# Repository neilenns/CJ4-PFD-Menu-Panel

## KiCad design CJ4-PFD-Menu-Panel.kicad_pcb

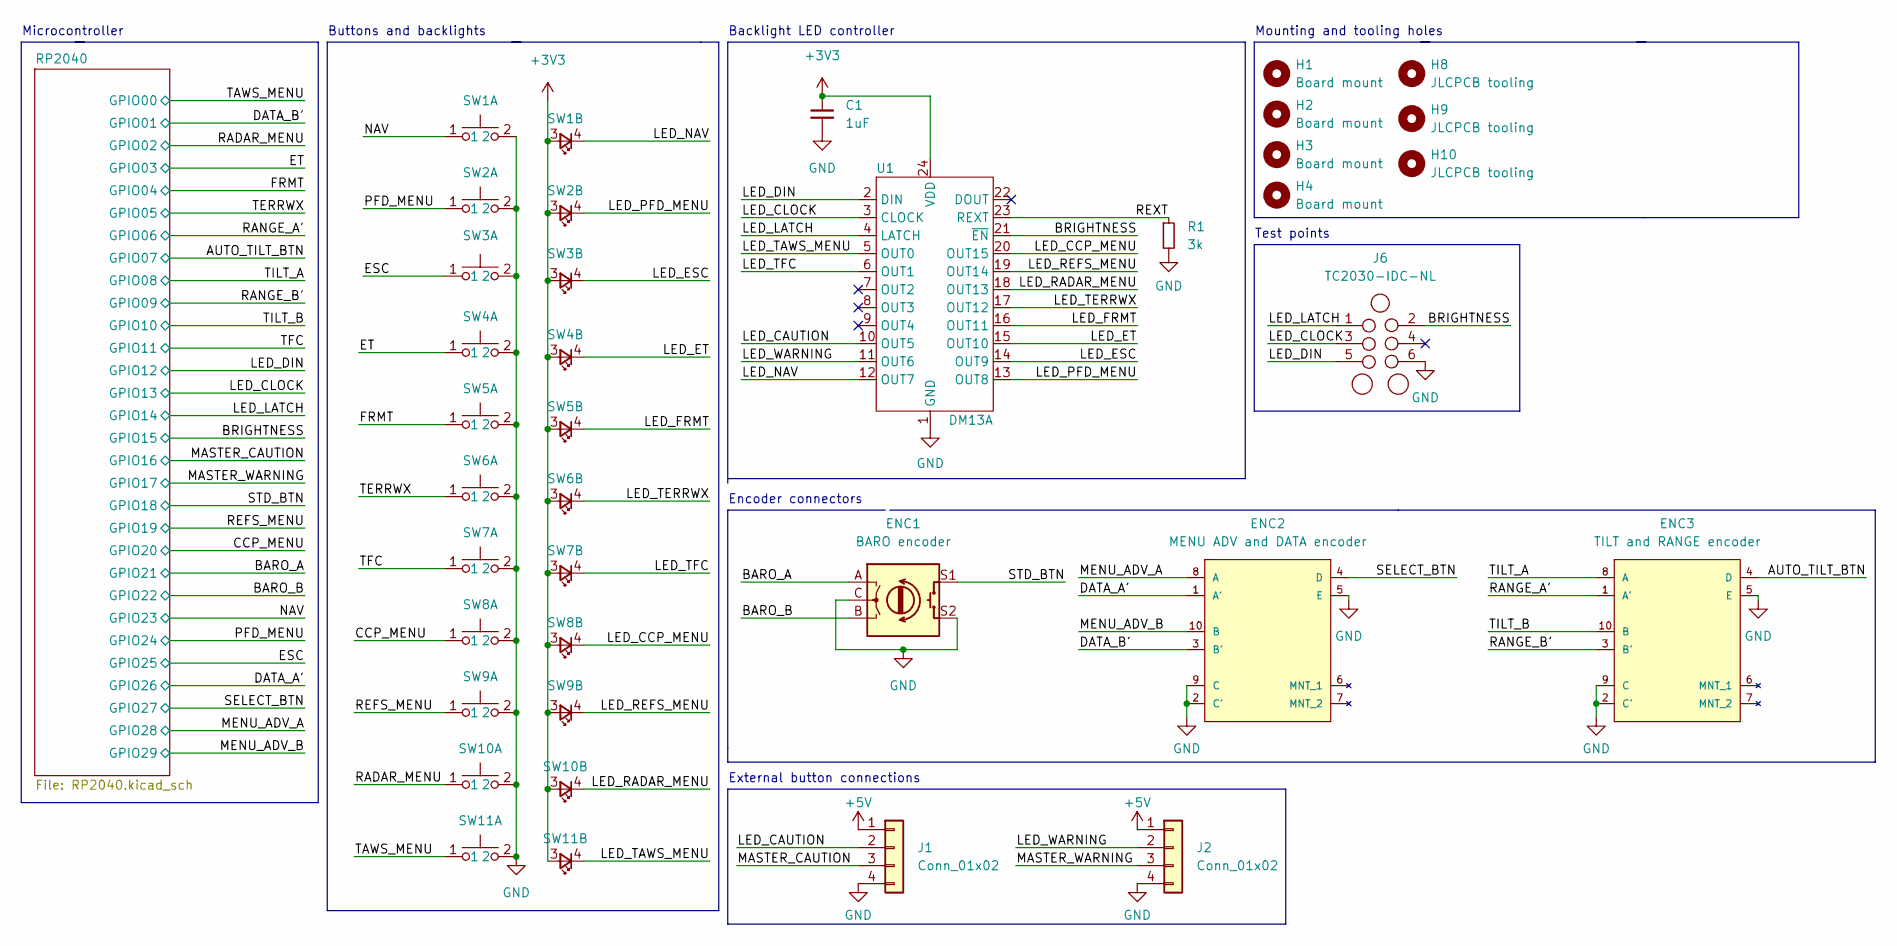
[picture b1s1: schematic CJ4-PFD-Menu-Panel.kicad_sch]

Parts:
C1: 1uF; Perfect_0402; JLC 0402
ENC1: BARO encoder; EN11-HSM1BF20_THT
ENC2: MENU ADV and DATA encoder; ALPS-EC11EBB24C03-0; Rating 10mA 5VDC; mouser part number 688-EC11EBB24C03
ENC3: TILT and RANGE encoder; ALPS-EC11EBB24C03-0; Rating 10mA 5VDC; mouser part number 688-EC11EBB24C03
H1, H2, H3, H4: Board mount; MountingHole_3.2mm_M3
H8, H9, H10: JLCPCB tooling; JLCPCB_Tooling_Hole
J1, J2: Conn_01x02; JST_XH_B4B-XH-A_1x04_P2.50mm_Vertical
J6: TC2030-IDC-NL; Tag-Connect_TC2030-IDC-NL_2x03_P1.27mm_Vertical
R1: 3k; R_0805_2012Metric_Pad1.20x1.40mm_HandSolder; JLC 0805
SW1, SW2, SW3, SW4, SW5, SW6, SW7, SW8, SW9, SW10, SW11: SW_PUSH_LED; SW_PUSH_LED_THT
U1: DM13A; SSOP-24_3.9x8.7mm_P0.635mm

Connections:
+3V3: C1.1, SW1.3, SW2.3, SW3.3, SW4.3, SW5.3, SW6.3, SW7.3, SW8.3, SW9.3, SW10.3, SW11.3, U1.24 (VDD); also elsewhere on the board
+5V: J1.1, J2.1; also elsewhere on the board
/AUTO_TILT_BTN: ENC3.4 (D); also elsewhere on the board
/BARO_A: ENC1.A; also elsewhere on the board
/BARO_B: ENC1.B; also elsewhere on the board
/BRIGHTNESS: J6.2, U1.21 (~EN); also elsewhere on the board
/CCP_MENU: SW8.1; also elsewhere on the board
/DATA_A': ENC2.1 (A'); also elsewhere on the board
/DATA_B': ENC2.3 (B'); also elsewhere on the board
/ESC: SW3.1; also elsewhere on the board
/ET: SW4.1; also elsewhere on the board
/FRMT: SW5.1; also elsewhere on the board
/LED_CAUTION: J1.2, U1.10 (OUT5)
/LED_CCP_MENU: SW8.4, U1.20 (OUT15)
/LED_CLOCK: J6.3, U1.3 (CLOCK); also elsewhere on the board
/LED_DIN: J6.5, U1.2 (DIN); also elsewhere on the board
/LED_ESC: SW3.4, U1.14 (OUT9)
/LED_ET: SW4.4, U1.15 (OUT10)
/LED_FRMT: SW5.4, U1.16 (OUT11)
/LED_LATCH: J6.1, U1.4 (LATCH); also elsewhere on the board
/LED_NAV: SW1.4, U1.12 (OUT7)
/LED_PFD_MENU: SW2.4, U1.13 (OUT8)
/LED_RADAR_MENU: SW10.4, U1.18 (OUT13)
/LED_REFS_MENU: SW9.4, U1.19 (OUT14)
/LED_TAWS_MENU: SW11.4, U1.5 (OUT0)
/LED_TERRWX: SW6.4, U1.17 (OUT12)
/LED_TFC: SW7.4, U1.6 (OUT1)
/LED_WARNING: J2.2, U1.11 (OUT6)
/MASTER_CAUTION: J1.3; also elsewhere on the board
/MASTER_WARNING: J2.3; also elsewhere on the board
/MENU_ADV_A: ENC2.8 (A); also elsewhere on the board
/MENU_ADV_B: ENC2.10 (B); also elsewhere on the board
/NAV: SW1.1; also elsewhere on the board
/PFD_MENU: SW2.1; also elsewhere on the board
/RADAR_MENU: SW10.1; also elsewhere on the board
/RANGE_A': ENC3.1 (A'); also elsewhere on the board
/RANGE_B': ENC3.3 (B'); also elsewhere on the board
/REFS_MENU: SW9.1; also elsewhere on the board
/REXT: R1.1, U1.23 (REXT)
/SELECT_BTN: ENC2.4 (D); also elsewhere on the board
/STD_BTN: ENC1.S1; also elsewhere on the board
/TAWS_MENU: SW11.1; also elsewhere on the board
/TERRWX: SW6.1; also elsewhere on the board
/TFC: SW7.1; also elsewhere on the board
/TILT_A: ENC3.8 (A); also elsewhere on the board
/TILT_B: ENC3.10 (B); also elsewhere on the board
GND: C1.2, ENC1.C, ENC1.S2, ENC2.2 (C'), ENC2.5 (E), ENC2.9 (C), ENC3.2 (C'), ENC3.5 (E), ENC3.9 (C), J1.4, J2.4, J6.6, R1.2, SW1.2, SW2.2, SW3.2, SW4.2, SW5.2, SW6.2, SW7.2, SW8.2, SW9.2, SW10.2, SW11.2, U1.1 (GND); also elsewhere on the board

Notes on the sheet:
Mounting and tooling holes
Microcontroller
Buttons and backlights
Backlight LED controller
Test points
Encoder connectors
External button connections

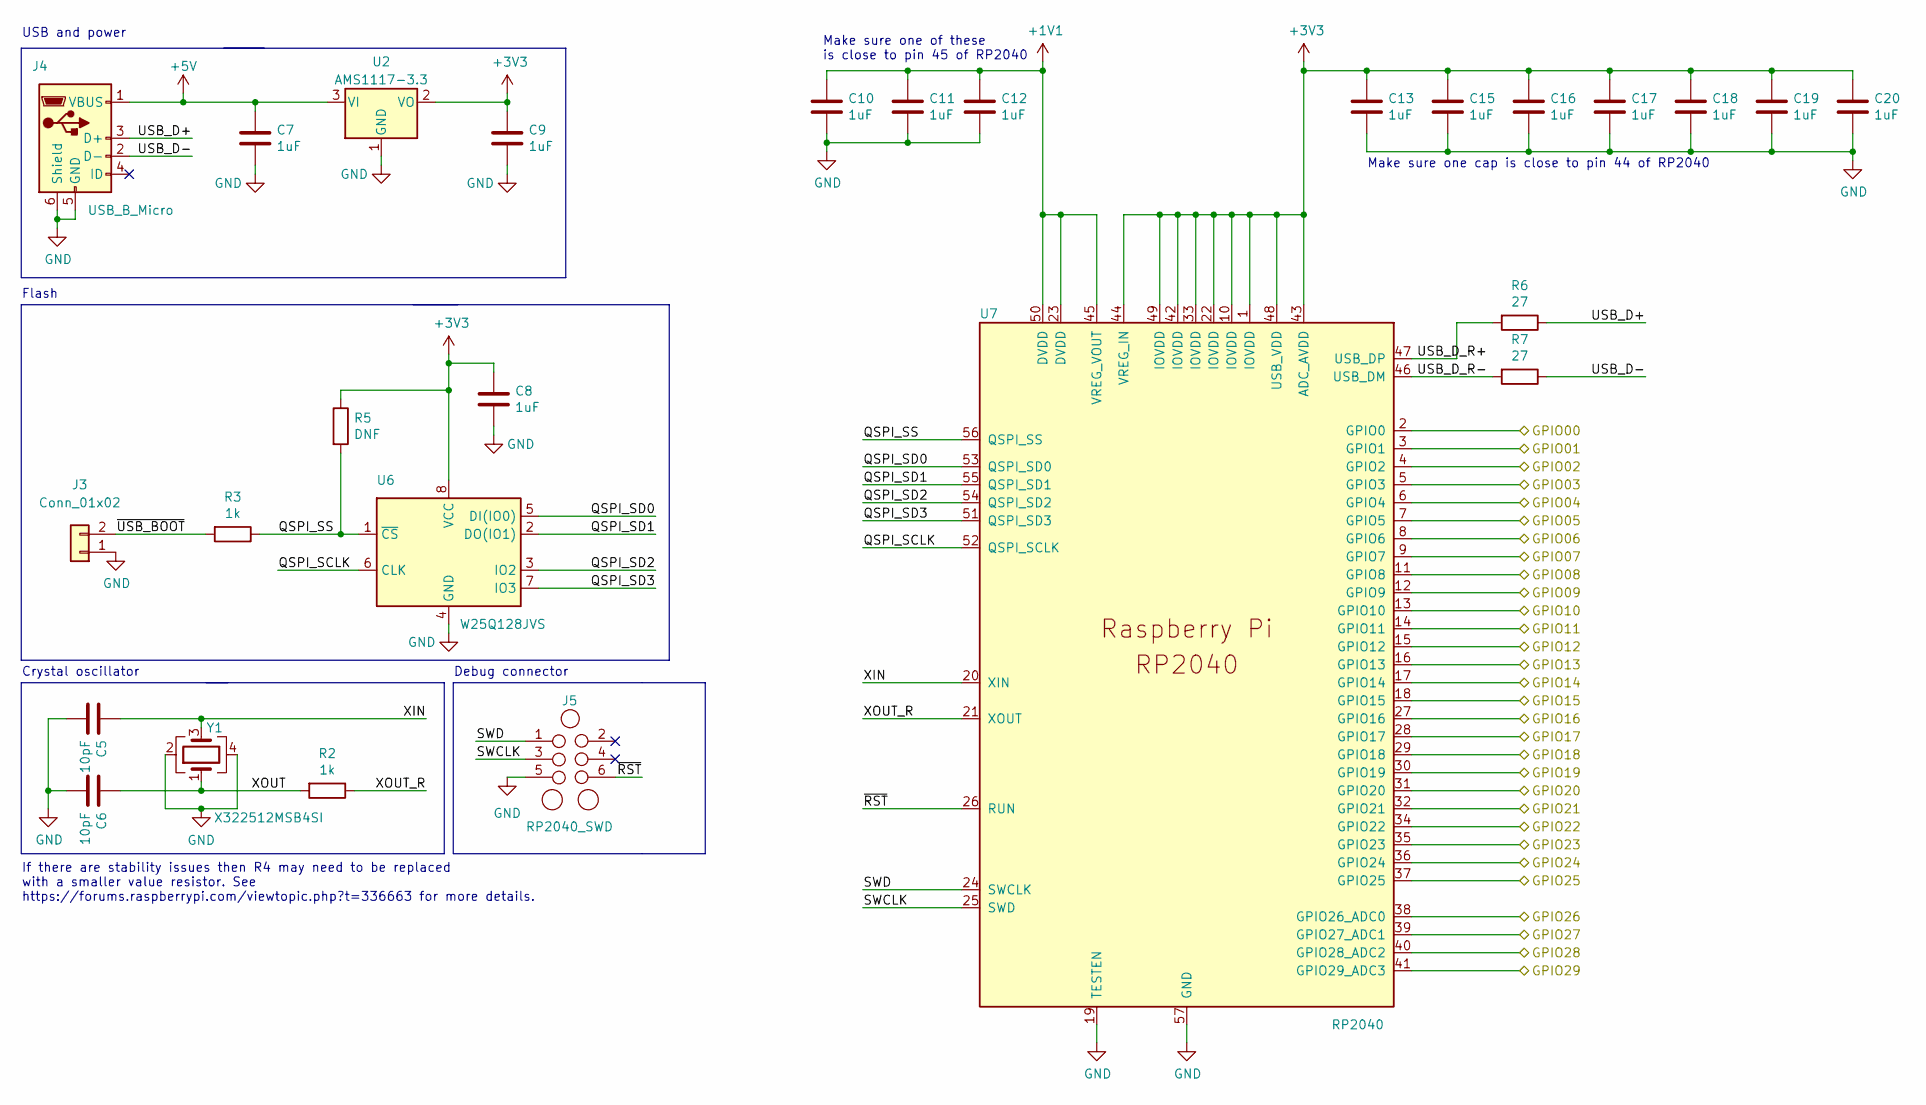
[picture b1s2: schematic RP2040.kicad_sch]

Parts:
C5, C6: 10pF; Perfect_0402; JLC 0402
C7, C8, C9, C10, C11, C12, C13, C15, C16, C17, C18, C19, C20: 1uF; Perfect_0402; JLC 0402
J3: Conn_01x02; PinHeader_1x02_P2.54mm_Vertical
J4: USB_B_Micro; USB_B_Mini_Amphenol_UE25BE5510H
J5: RP2040_SWD; Tag-Connect_TC2030-IDC-NL_2x03_P1.27mm_Vertical
R2, R3: 1k; Perfect_0402; JLC 0402
R5: DNF; R_1206_3216Metric_Pad1.30x1.75mm_HandSolder
R6, R7: 27; R_0603_1608Metric; JLC 0603
U2: AMS1117-3.3; SOT-223-3_TabPin2; JLC SOT-223
U6: W25Q128JVS; SOIC-8_5.23x5.23mm_P1.27mm; JLC SOIC-8-208mil
U7: RP2040; QFN56P40_700X700X90L40X18T310N; JLC LQFN-56_EP_7.0x7.0x0.4P
Y1: X322512MSB4SI; Crystal_SMD_3225-4Pin_3.2x2.5mm; JLC SMD-3225_4P

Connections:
+1V1: C10.1, C11.1, C12.1, U7.23 (DVDD), U7.45 (VREG_VOUT), U7.50 (DVDD)
+3V3: C8.1, C9.1, C13.1, C15.1, C16.1, C17.1, C18.1, C19.1, C20.1, R5.1, U2.2 (VO), U6.8 (VCC), U7.1 (IOVDD), U7.10 (IOVDD), U7.22 (IOVDD), U7.33 (IOVDD), U7.42 (IOVDD), U7.43 (ADC_AVDD), U7.44 (VREG_IN), U7.48 (USB_VDD), U7.49 (IOVDD); also elsewhere on the board
+5V: C7.1, J4.1 (VBUS), U2.3 (VI); also elsewhere on the board
/AUTO_TILT_BTN: U7.9 (GPIO7); also elsewhere on the board
/BARO_A: U7.32 (GPIO21); also elsewhere on the board
/BARO_B: U7.34 (GPIO22); also elsewhere on the board
/BRIGHTNESS: U7.18 (GPIO15); also elsewhere on the board
/CCP_MENU: U7.31 (GPIO20); also elsewhere on the board
/DATA_A': U7.38 (GPIO26_ADC0); also elsewhere on the board
/DATA_B': U7.3 (GPIO1); also elsewhere on the board
/ESC: U7.37 (GPIO25); also elsewhere on the board
/ET: U7.5 (GPIO3); also elsewhere on the board
/FRMT: U7.6 (GPIO4); also elsewhere on the board
/LED_CLOCK: U7.16 (GPIO13); also elsewhere on the board
/LED_DIN: U7.15 (GPIO12); also elsewhere on the board
/LED_LATCH: U7.17 (GPIO14); also elsewhere on the board
/MASTER_CAUTION: U7.27 (GPIO16); also elsewhere on the board
/MASTER_WARNING: U7.28 (GPIO17); also elsewhere on the board
/MENU_ADV_A: U7.40 (GPIO28_ADC2); also elsewhere on the board
/MENU_ADV_B: U7.41 (GPIO29_ADC3); also elsewhere on the board
/NAV: U7.35 (GPIO23); also elsewhere on the board
/PFD_MENU: U7.36 (GPIO24); also elsewhere on the board
/RADAR_MENU: U7.4 (GPIO2); also elsewhere on the board
/RANGE_A': U7.8 (GPIO6); also elsewhere on the board
/RANGE_B': U7.12 (GPIO9); also elsewhere on the board
/REFS_MENU: U7.30 (GPIO19); also elsewhere on the board
/RP2040/QSPI_SCLK: U6.6 (CLK), U7.52 (QSPI_SCLK)
/RP2040/QSPI_SD0: U6.5 (DI(IO0)), U7.53 (QSPI_SD0)
/RP2040/QSPI_SD1: U6.2 (DO(IO1)), U7.55 (QSPI_SD1)
/RP2040/QSPI_SD2: U6.3 (IO2), U7.54 (QSPI_SD2)
/RP2040/QSPI_SD3: U6.7 (IO3), U7.51 (QSPI_SD3)
/RP2040/QSPI_SS: R3.1, R5.2, U6.1 (~CS), U7.56 (QSPI_SS)
/RP2040/SWCLK: J5.3, U7.25 (SWD)
/RP2040/SWD: J5.1, U7.24 (SWCLK)
/RP2040/USB_D+: J4.3 (D+), R6.1
/RP2040/USB_D-: J4.2 (D-), R7.1
/RP2040/USB_D_R+: R6.2, U7.47 (USB_DP)
/RP2040/USB_D_R-: R7.2, U7.46 (USB_DM)
/RP2040/XIN: C5.1, U7.20 (XIN), Y1.3
/RP2040/XOUT: C6.1, R2.2, Y1.1
/RP2040/XOUT_R: R2.1, U7.21 (XOUT)
/RP2040/~RST: J5.6, U7.26 (RUN)
/RP2040/~USB_BOOT: J3.2, R3.2
/SELECT_BTN: U7.39 (GPIO27_ADC1); also elsewhere on the board
/STD_BTN: U7.29 (GPIO18); also elsewhere on the board
/TAWS_MENU: U7.2 (GPIO0); also elsewhere on the board
/TERRWX: U7.7 (GPIO5); also elsewhere on the board
/TFC: U7.14 (GPIO11); also elsewhere on the board
/TILT_A: U7.11 (GPIO8); also elsewhere on the board
/TILT_B: U7.13 (GPIO10); also elsewhere on the board
GND: C5.2, C6.2, C7.2, C8.2, C9.2, C10.2, C11.2, C12.2, C13.2, C15.2, C16.2, C17.2, C18.2, C19.2, C20.2, J3.1, J4.5 (GND), J4.6 (Shield), J5.5, U2.1 (GND), U6.4 (GND), U7.19 (TESTEN), U7.57 (GND), Y1.2, Y1.4; also elsewhere on the board

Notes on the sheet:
If there are stability issues then R4 may need to be replaced with a smaller value resistor. See https://forums.raspberrypi.com/viewtopic.php?t=336663 for more details.
Make sure one cap is close to pin 44 of RP2040
Crystal oscillator
USB and power
Flash
Debug connector
Make sure one of these is close to pin 45 of RP2040

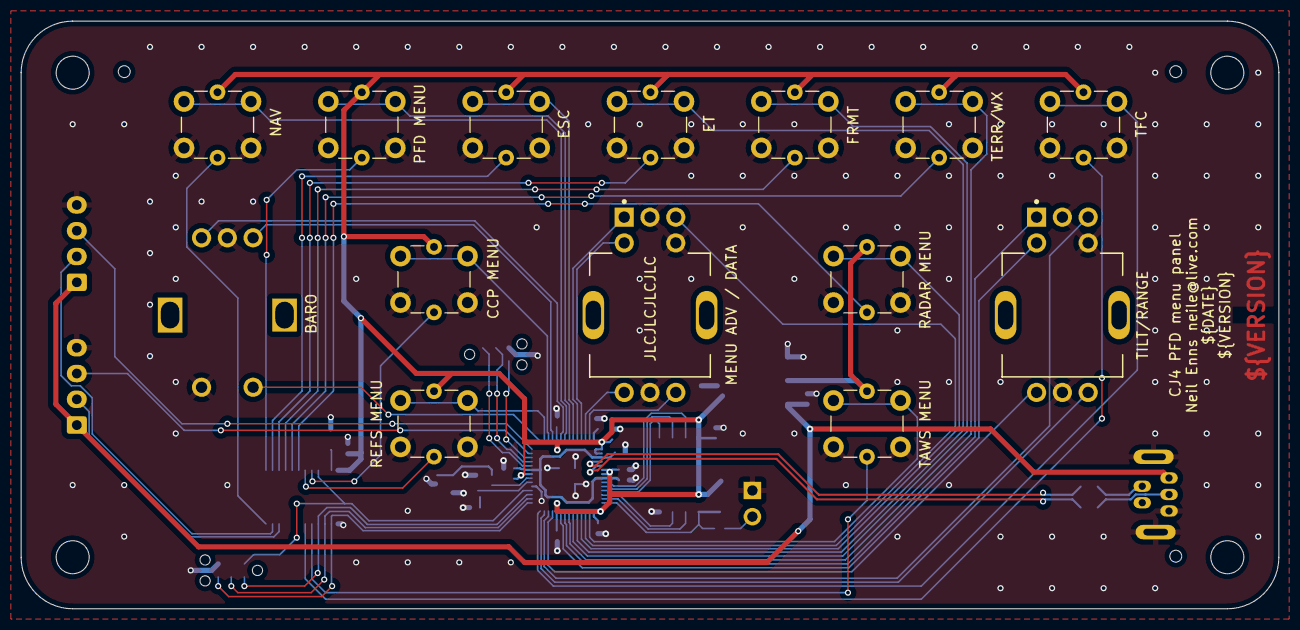
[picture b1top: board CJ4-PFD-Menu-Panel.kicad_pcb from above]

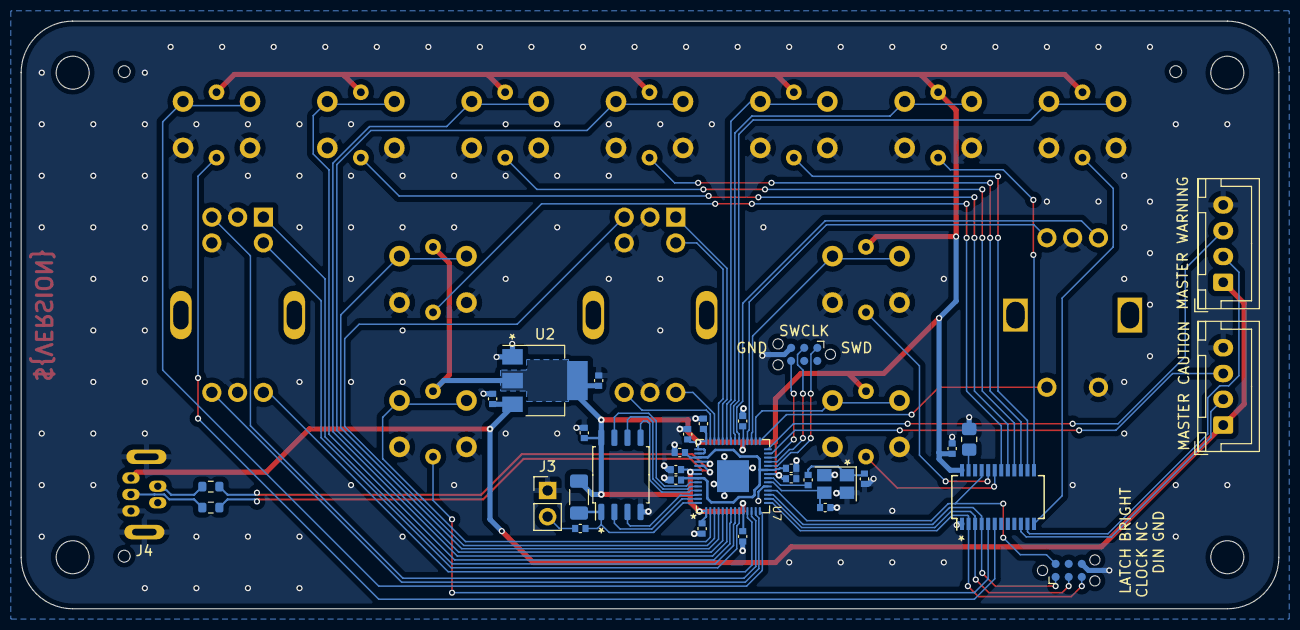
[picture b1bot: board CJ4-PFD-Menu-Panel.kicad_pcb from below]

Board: 2 copper layers, 122.0 x 57.0 mm, 54 parts (36 on the bottom side), 65 nets.

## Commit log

2022-12-04 RP2040 design
2022-12-04 Add TCA8418
2022-12-04 Expose the GPIO pins
2022-12-04 Buttons and LED driver
2022-12-05 Initial schematic complete
2022-12-06 More updates
2022-12-06 Some board layout work
2022-12-12 Redo RP2040 layout
2022-12-12 Fully routed!
2022-12-12 Update external button connector, 3d models
2022-12-12 Cleanup silkscreen and version/date
2022-12-12 Silkscreen and date/version stuff
2022-12-12 Oops
2022-12-13 Fix encoder wiring
2022-12-13 Add debug connections
2022-12-14 Final changes prior to ordering
2022-12-14 Update part rotation
2022-12-14 Fix copper fill, add via stitching
2022-12-16 Add MobiFlight configuration files
2022-12-29 Fix the footprints, add stuff
2025-02-25 Add renovate.json
